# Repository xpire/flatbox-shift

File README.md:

# Hotbox: Low profile hitbox-layout fightstick
## This is a fork of Flatbox, where the PCB was modified to have a shift along with the directional inputs, and use hotswappable fullsize MX key switches

This repository contains 3D-printable models, PCB design files and code needed to make an arcade controller that looks like this:

Look at the table for the difference between each revision.

Reddit post: https://www.reddit.com/r/fightsticks/comments/y1vh9n/my_custom_fight_stick_made_with_a_custom_pcb_7/

version | [rev1.1](hardware-rev1.1) | [rev2](hardware-rev2) | [rev3](hardware-rev3) | [rev4](hardware-rev4) | [shift](hardware-shift-rev2)
------- | ------------------------- | --------------------- | --------------------- | --------------------- | ----
case dimensions | 218x128x10mm | 218x130x10mm | 218x130x10mm | 218x130x10mm | 227.14x120x?mm
compatibility (using provided firmware) | PC, PS3 | PC, PS3 | PC, PS3, PS4 | PC, PS3 | PC, PS3
add-on board | Arduino Pro Micro | - | [Brook PS3/PS4](https://www.brookaccessory.com/detail/58690501/) | - | Arduino Pro Micro
onboard chip | - | ATmega32U4 | - | RP2040 | - 
port | micro USB | USB-C | USB-C | USB-C | USB-C (there are pro micros with usb c)
SMT assembly required | no | yes | yes | yes | no
firmware | [ATmega32U4](firmware-atmega32u4) | [ATmega32U4](firmware-atmega32u4) | [Brook](https://www.brookaccessory.com/download/PS3/) | [RP2040](firmware-rp2040) | [ATmega32U4](firmware-atmega32u4)
shift key | no | no | no | no | ***yes!***
key switches | low profile | low profile | low profile | low profile | ***normal MX***
hot swappable | yes | yes | yes | yes | yes
solder-able | yes | yes | yes | yes | no

# Process

## Design and Planning

First, we used Kicad to edit this existing PCB layout, adding an extra button for shift and swapping out the low profile gaterons for full sized MX hotswap.

We then designed acrylic layers to encase the PCB, and mocked it in blender to see if it would work out.

## Prototyping

We printed the boards with https://jlcpcb.com/

We soldered on the arduino, and tested that the inputs worked

Once we had verified the board worked, we 3D printed the layers to simulate what the final product would look like.

## Fabrication

We borrowed a friend's uncle's CNC machine, and started carving the design out of sheets of acrylic.

## Result

## Parts List
* arcade MX buttons - https://www.ebay.com/itm/165134564232 (url is now https://www.ebay.com/itm/155628299989)
* Chicago Screws - https://www.ebay.com/itm/0-67-034-to-0-87-034-17mm-to-22-mm-x-5mm-Stainless-steel-Knife-Handle-chicago-Screw-/231976520482?ssPageName=STRK:MESE:IT
* MX Switches
* Gateron hotswaps
* mini buttons
* Arduino pro micro with usb c
* Acrylic Layers (laser cut, or CNCed)

## Useful guides
- https://github.com/b1nc/Egg-On-Rice-Controller
- https://www.youtube.com/watch?v=ia2n7P3Csac

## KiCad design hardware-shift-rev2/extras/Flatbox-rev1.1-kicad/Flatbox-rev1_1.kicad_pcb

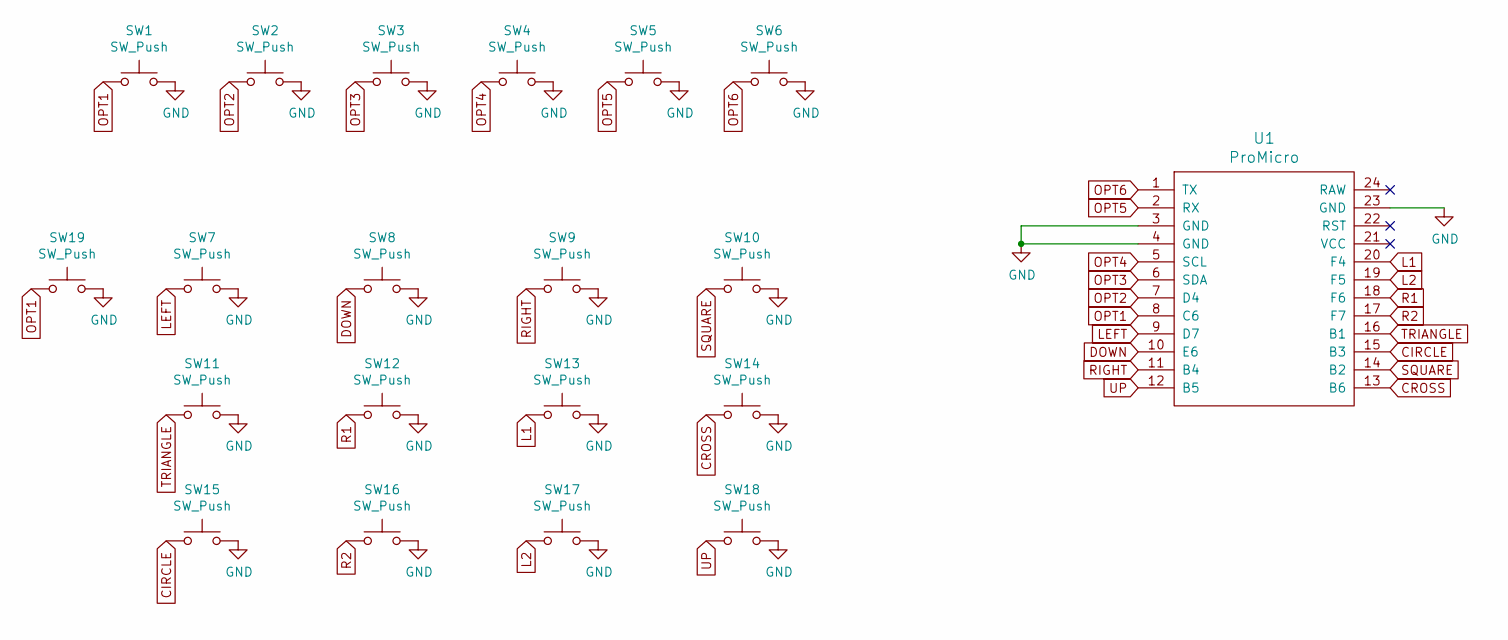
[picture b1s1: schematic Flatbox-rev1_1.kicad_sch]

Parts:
SW1, SW2, SW3, SW4, SW5, SW6: SW_Push; SW_PUSH_6mm_H5mm
SW7, SW8, SW9, SW10, SW11, SW12, SW13, SW14, SW15, SW16, SW17, SW18, SW19: SW_Push; SW_Hotswap_Kailh_MX_plated_1.00u
U1: ProMicro

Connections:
CIRCLE: SW15.1, U1.15 (B3)
CROSS: SW14.1, U1.13 (B6)
DOWN: SW8.1, U1.10 (E6)
GND: SW1.2, SW2.2, SW3.2, SW4.2, SW5.2, SW6.2, SW7.2, SW8.2, SW9.2, SW10.2, SW11.2, SW12.2, SW13.2, SW14.2, SW15.2, SW16.2, SW17.2, SW18.2, SW19.2, U1.3 (GND), U1.4 (GND), U1.23 (GND)
L1: SW13.1, U1.20 (F4)
L2: SW17.1, U1.19 (F5)
LEFT: SW7.1, U1.9 (D7)
OPT1: SW1.1, SW19.1, U1.8 (C6)
OPT2: SW2.1, U1.7 (D4)
OPT3: SW3.1, U1.6 (SDA)
OPT4: SW4.1, U1.5 (SCL)
OPT5: SW5.1, U1.2 (RX)
OPT6: SW6.1, U1.1 (TX)
R1: SW12.1, U1.18 (F6)
R2: SW16.1, U1.17 (F7)
RIGHT: SW9.1, U1.11 (B4)
SQUARE: SW10.1, U1.14 (B2)
TRIANGLE: SW11.1, U1.16 (B1)
UP: SW18.1, U1.12 (B5)

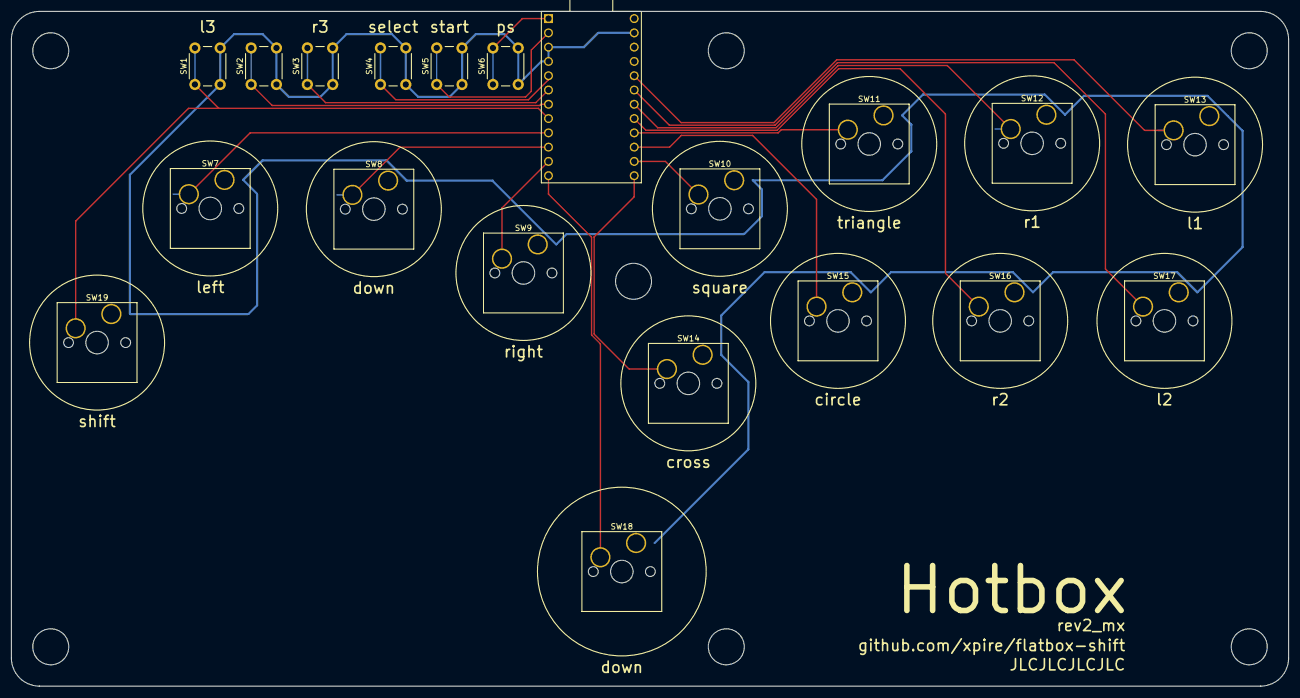
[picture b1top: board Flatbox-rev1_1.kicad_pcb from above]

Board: 2 copper layers, 227.1 x 120.0 mm, 20 parts (0 on the bottom side), 19 nets.

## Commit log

2022-08-14 modify pcb with left shift
2022-08-14 add some details to readme
2022-08-14 new version with modified action keys and parallel R3/shift
2022-08-14 parallel action keys
2022-08-14 3rd action keys up, top by 3mm, bottom by 4mm
2022-08-14 smaller tolerance tilted
2022-08-14 added key labels
2022-08-14 no wires rev2 (please position now)
2022-08-14 minimal changes should work 100% because i changed literally nothing
2022-08-16 finalised MX compatiable hotswap pcb
2022-08-16 step file uploaded
2022-08-17 Add layer1.dxf
2022-08-17 clean up folders
2022-08-17 Remove random arc
2022-08-17 add readme info
2023-08-05 Add layers and pictures of construction
2023-08-05 add jpg result images
2023-08-05 add process jpg
